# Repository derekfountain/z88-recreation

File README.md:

# z88-recreation
A recreation of the 1980's Z88 micro, using modern components

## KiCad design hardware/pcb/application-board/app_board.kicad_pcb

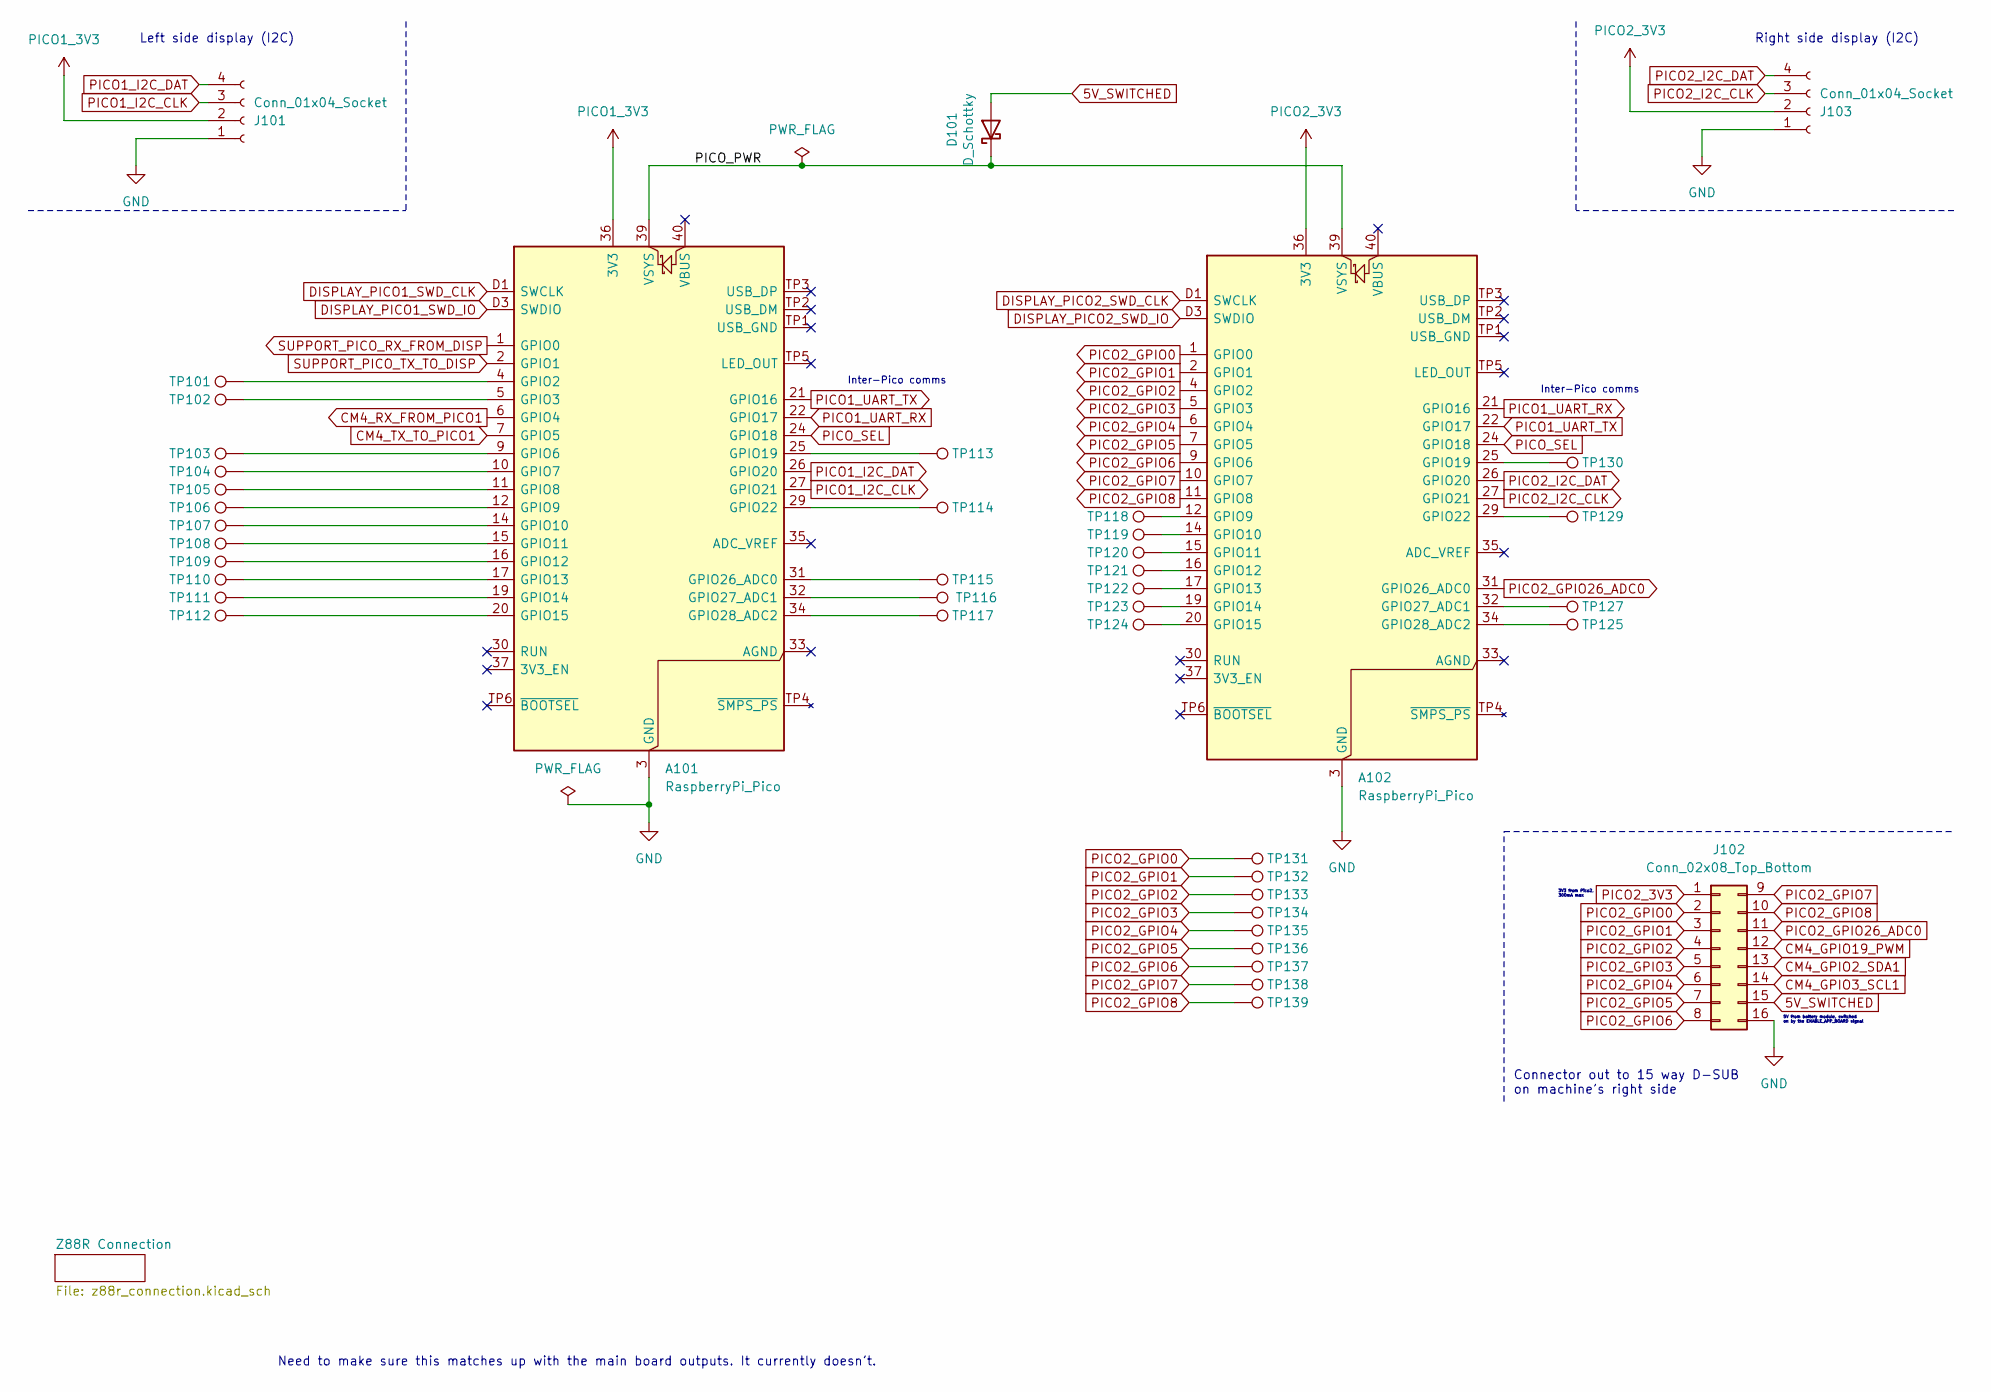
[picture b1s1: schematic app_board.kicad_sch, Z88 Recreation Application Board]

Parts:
A101, A102: RaspberryPi_Pico; RaspberryPi_Pico_Original_SMD
D101: D_Schottky; D_1206_3216Metric_Pad1.42x1.75mm_HandSolder
J101, J103: Conn_01x04_Socket; PinHeader_1x04_P2.54mm_Vertical
J102: Conn_02x08_Top_Bottom; PinHeader_2x08_P2.54mm_Vertical
TP101, TP102, TP103, TP104, TP105, TP106, TP107, TP108, TP109, TP110, TP111, TP112, TP113, TP114, TP115, TP116, TP117, TP118, TP119, TP120, TP121, TP122, TP123, TP124, TP125, TP127, TP129, TP130, TP131, TP132, TP133, TP134, TP135, TP136, TP137, TP138, TP139: TestPoint; TestPoint_THTPad_D2.0mm_Drill1.0mm

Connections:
5V_SWITCHED: D101.2 (A), J102.15; also elsewhere on the board
/PICO_PWR: A101.39 (VSYS), A102.39 (VSYS), D101.1 (K)
CM4_GPIO2_SDA1: J102.13; also elsewhere on the board
CM4_GPIO3_SCL1: J102.14; also elsewhere on the board
CM4_GPIO19_PWM: J102.12; also elsewhere on the board
CM4_RX_FROM_PICO1: A101.6 (GPIO4); also elsewhere on the board
CM4_TX_TO_PICO1: A101.7 (GPIO5); also elsewhere on the board
DISPLAY_PICO1_SWD_CLK: A101.D1 (SWCLK); also elsewhere on the board
DISPLAY_PICO1_SWD_IO: A101.D3 (SWDIO); also elsewhere on the board
DISPLAY_PICO2_SWD_CLK: A102.D1 (SWCLK); also elsewhere on the board
DISPLAY_PICO2_SWD_IO: A102.D3 (SWDIO); also elsewhere on the board
GND: A101.3 (GND), A101.8 (GND), A101.13 (GND), A101.18 (GND), A101.23 (GND), A101.28 (GND), A101.38 (GND), A101.D2 (GND), A102.3 (GND), A102.8 (GND), A102.13 (GND), A102.18 (GND), A102.23 (GND), A102.28 (GND), A102.38 (GND), A102.D2 (GND), J101.1, J102.16, J103.1; also elsewhere on the board
unnamed: A101.4 (GPIO2), TP101.1
unnamed: A101.5 (GPIO3), TP102.1
unnamed: A101.9 (GPIO6), TP103.1
unnamed: A101.10 (GPIO7), TP104.1
unnamed: A101.11 (GPIO8), TP105.1
unnamed: A101.12 (GPIO9), TP106.1
unnamed: A101.14 (GPIO10), TP107.1
unnamed: A101.15 (GPIO11), TP108.1
unnamed: A101.16 (GPIO12), TP109.1
unnamed: A101.17 (GPIO13), TP110.1
unnamed: A101.19 (GPIO14), TP111.1
unnamed: A101.20 (GPIO15), TP112.1
unnamed: A101.25 (GPIO19), TP113.1
unnamed: A101.29 (GPIO22), TP114.1
unnamed: A101.31 (GPIO26_ADC0), TP115.1
unnamed: A101.32 (GPIO27_ADC1), TP116.1
unnamed: A101.34 (GPIO28_ADC2), TP117.1
unnamed: A102.12 (GPIO9), TP118.1
unnamed: A102.14 (GPIO10), TP119.1
unnamed: A102.15 (GPIO11), TP120.1
unnamed: A102.16 (GPIO12), TP121.1
unnamed: A102.17 (GPIO13), TP122.1
unnamed: A102.19 (GPIO14), TP123.1
unnamed: A102.20 (GPIO15), TP124.1
unnamed: A102.25 (GPIO19), TP130.1
unnamed: A102.29 (GPIO22), TP129.1
unnamed: A102.32 (GPIO27_ADC1), TP127.1
unnamed: A102.34 (GPIO28_ADC2), TP125.1
PICO1_3V3: A101.36 (3V3), J101.2
PICO1_I2C_CLK: A101.27 (GPIO21), J101.3
PICO1_I2C_DAT: A101.26 (GPIO20), J101.4
PICO1_UART_RX: A101.22 (GPIO17), A102.21 (GPIO16)
PICO1_UART_TX: A101.21 (GPIO16), A102.22 (GPIO17)
PICO2_3V3: A102.36 (3V3), J102.1, J103.2
PICO2_GPIO0: A102.1 (GPIO0), J102.2, TP131.1
PICO2_GPIO1: A102.2 (GPIO1), J102.3, TP132.1
PICO2_GPIO2: A102.4 (GPIO2), J102.4, TP133.1
PICO2_GPIO3: A102.5 (GPIO3), J102.5, TP134.1
PICO2_GPIO4: A102.6 (GPIO4), J102.6, TP135.1
PICO2_GPIO5: A102.7 (GPIO5), J102.7, TP136.1
PICO2_GPIO6: A102.9 (GPIO6), J102.8, TP137.1
PICO2_GPIO7: A102.10 (GPIO7), J102.9, TP138.1
PICO2_GPIO8: A102.11 (GPIO8), J102.10, TP139.1
PICO2_GPIO26_ADC0: A102.31 (GPIO26_ADC0), J102.11
PICO2_I2C_CLK: A102.27 (GPIO21), J103.3
PICO2_I2C_DAT: A102.26 (GPIO20), J103.4
PICO_SEL: A101.24 (GPIO18), A102.24 (GPIO18); also elsewhere on the board
SUPPORT_PICO_RX_FROM_DISP: A101.1 (GPIO0); also elsewhere on the board
SUPPORT_PICO_TX_TO_DISP: A101.2 (GPIO1); also elsewhere on the board

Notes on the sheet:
3V3 from Pico2, 300mA max
Connector out to 15 way D-SUB on machine's right side
Right side display (I2C)
5V from battery module, switched on by the ENABLE_APP_BOARD signal
Inter-Pico comms
Need to make sure this matches up with the main board outputs. It currently doesn't.
Left side display (I2C)

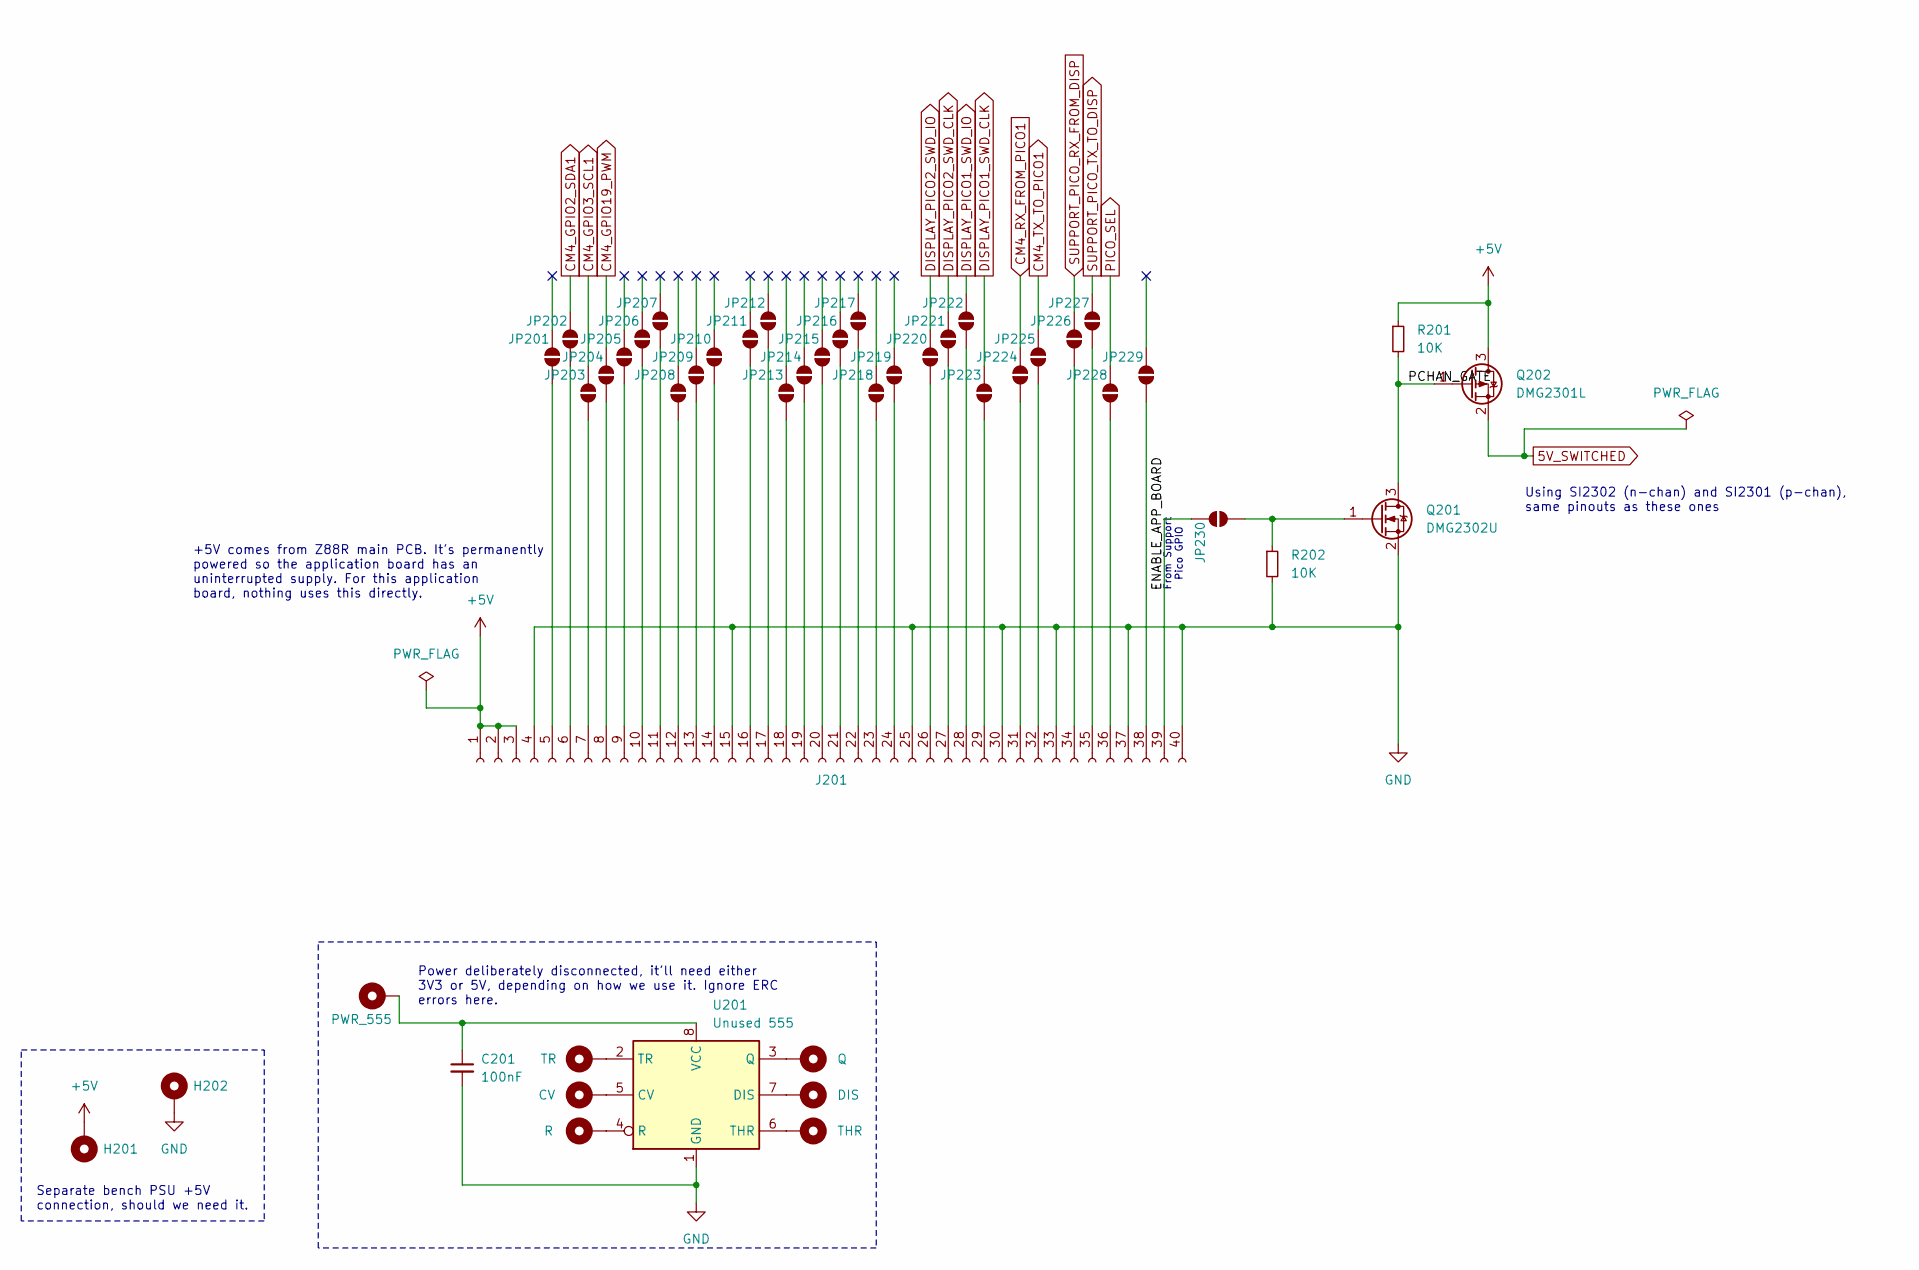
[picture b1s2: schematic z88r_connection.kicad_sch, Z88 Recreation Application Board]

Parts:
C201: 100nF; C_0805_2012Metric_Pad1.18x1.45mm_HandSolder
H201: +5V; MountingHole_2.2mm_M2_Pad
H202: GND; MountingHole_2.2mm_M2_Pad
H203: PWR_555; Pin_D0.7mm_L6.5mm_W1.8mm_FlatFork
H204: TR; Pin_D0.7mm_L6.5mm_W1.8mm_FlatFork
H205: CV; Pin_D0.7mm_L6.5mm_W1.8mm_FlatFork
H206: R; Pin_D0.7mm_L6.5mm_W1.8mm_FlatFork
H207: Q; Pin_D0.7mm_L6.5mm_W1.8mm_FlatFork
H208: DIS; Pin_D0.7mm_L6.5mm_W1.8mm_FlatFork
H209: THR; Pin_D0.7mm_L6.5mm_W1.8mm_FlatFork
J201: DISP_PCB x40 FPC; Hirose_FH12-40S-0.5SH_1x40-1MP_P0.50mm_Horizontal
JP201, JP202, JP203, JP204, JP205, JP206, JP207, JP208, JP209, JP210, JP211, JP212, JP213, JP214, JP215, JP216, JP217, JP218, JP219, JP220, JP221, JP222, JP223, JP224, JP225, JP226, JP227, JP228, JP229, JP230: SolderJumper_2_Open; SolderJumper-2_P1.3mm_Open_Pad1.0x1.5mm
Q201: DMG2302U; SOT-23
Q202: DMG2301L; SOT-23
R201, R202: 10K; R_0805_2012Metric_Pad1.20x1.40mm_HandSolder
U201: Unused 555; SOIC-8_3.9x4.9mm_P1.27mm

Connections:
5V_SWITCHED: Q202.2 (S); also elsewhere on the board
+5V: H201.1, J201.1, J201.2, J201.3, Q202.3 (D), R201.1
/Z88R Connection/ENABLE_APP_BOARD: J201.39, JP230.2 (B)
/Z88R Connection/PCHAN_GATE: Q201.3 (D), Q202.1 (G), R201.2
CM4_GPIO2_SDA1: JP202.2 (B); also elsewhere on the board
CM4_GPIO3_SCL1: JP203.2 (B); also elsewhere on the board
CM4_GPIO19_PWM: JP204.2 (B); also elsewhere on the board
CM4_RX_FROM_PICO1: JP224.2 (B); also elsewhere on the board
CM4_TX_TO_PICO1: JP225.2 (B); also elsewhere on the board
DISPLAY_PICO1_SWD_CLK: JP223.2 (B); also elsewhere on the board
DISPLAY_PICO1_SWD_IO: JP222.2 (B); also elsewhere on the board
DISPLAY_PICO2_SWD_CLK: JP221.2 (B); also elsewhere on the board
DISPLAY_PICO2_SWD_IO: JP220.2 (B); also elsewhere on the board
GND: C201.2, H202.1, J201.4, J201.15, J201.25, J201.30, J201.33, J201.37, J201.40, Q201.2 (S), R202.2, U201.1 (GND); also elsewhere on the board
unnamed: J201.5, JP201.1 (A)
unnamed: J201.6, JP202.1 (A)
unnamed: J201.7, JP203.1 (A)
unnamed: J201.8, JP204.1 (A)
unnamed: J201.9, JP205.1 (A)
unnamed: J201.10, JP206.1 (A)
unnamed: J201.11, JP207.1 (A)
unnamed: J201.12, JP208.1 (A)
unnamed: J201.13, JP209.1 (A)
unnamed: J201.14, JP210.1 (A)
unnamed: J201.16, JP211.1 (A)
unnamed: J201.17, JP212.1 (A)
unnamed: J201.18, JP213.1 (A)
unnamed: J201.19, JP214.1 (A)
unnamed: J201.20, JP215.1 (A)
unnamed: J201.21, JP216.1 (A)
unnamed: J201.22, JP217.1 (A)
unnamed: J201.23, JP218.1 (A)
unnamed: J201.24, JP219.1 (A)
unnamed: J201.26, JP220.1 (A)
unnamed: J201.27, JP221.1 (A)
unnamed: J201.28, JP222.1 (A)
unnamed: J201.29, JP223.1 (A)
unnamed: J201.31, JP224.1 (A)
unnamed: J201.32, JP225.1 (A)
unnamed: J201.34, JP226.1 (A)
unnamed: J201.35, JP227.1 (A)
unnamed: J201.36, JP228.1 (A)
unnamed: J201.38, JP229.1 (A)
unnamed: JP230.1 (A), Q201.1 (G), R202.1
unnamed: H205.1, U201.5 (CV)
unnamed: H208.1, U201.7 (DIS)
unnamed: H207.1, U201.3 (Q)
unnamed: H206.1, U201.4 (R)
unnamed: H209.1, U201.6 (THR)
unnamed: H204.1, U201.2 (TR)
unnamed: C201.1, H203.1, U201.8 (VCC)
PICO_SEL: JP228.2 (B); also elsewhere on the board
SUPPORT_PICO_RX_FROM_DISP: JP226.2 (B); also elsewhere on the board
SUPPORT_PICO_TX_TO_DISP: JP227.2 (B); also elsewhere on the board

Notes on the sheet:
Separate bench PSU +5V connection, should we need it.
Using SI2302 (n-chan) and SI2301 (p-chan), same pinouts as these ones
Power deliberately disconnected, it'll need either 3V3 or 5V, depending on how we use it. Ignore ERC errors here.
+5V comes from Z88R main PCB. It's permanently powered so the application board has an uninterrupted supply. For this application board, nothing uses this directly.
From Support Pico GPIO

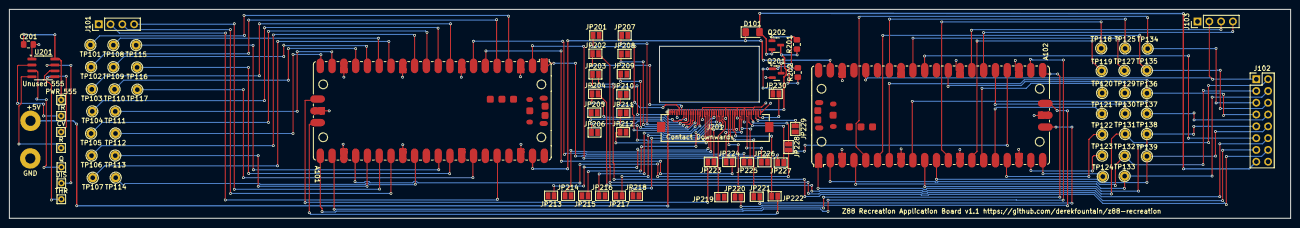
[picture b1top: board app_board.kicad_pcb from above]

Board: 2 copper layers, 276.0 x 45.0 mm, 89 parts (0 on the bottom side), 101 nets.

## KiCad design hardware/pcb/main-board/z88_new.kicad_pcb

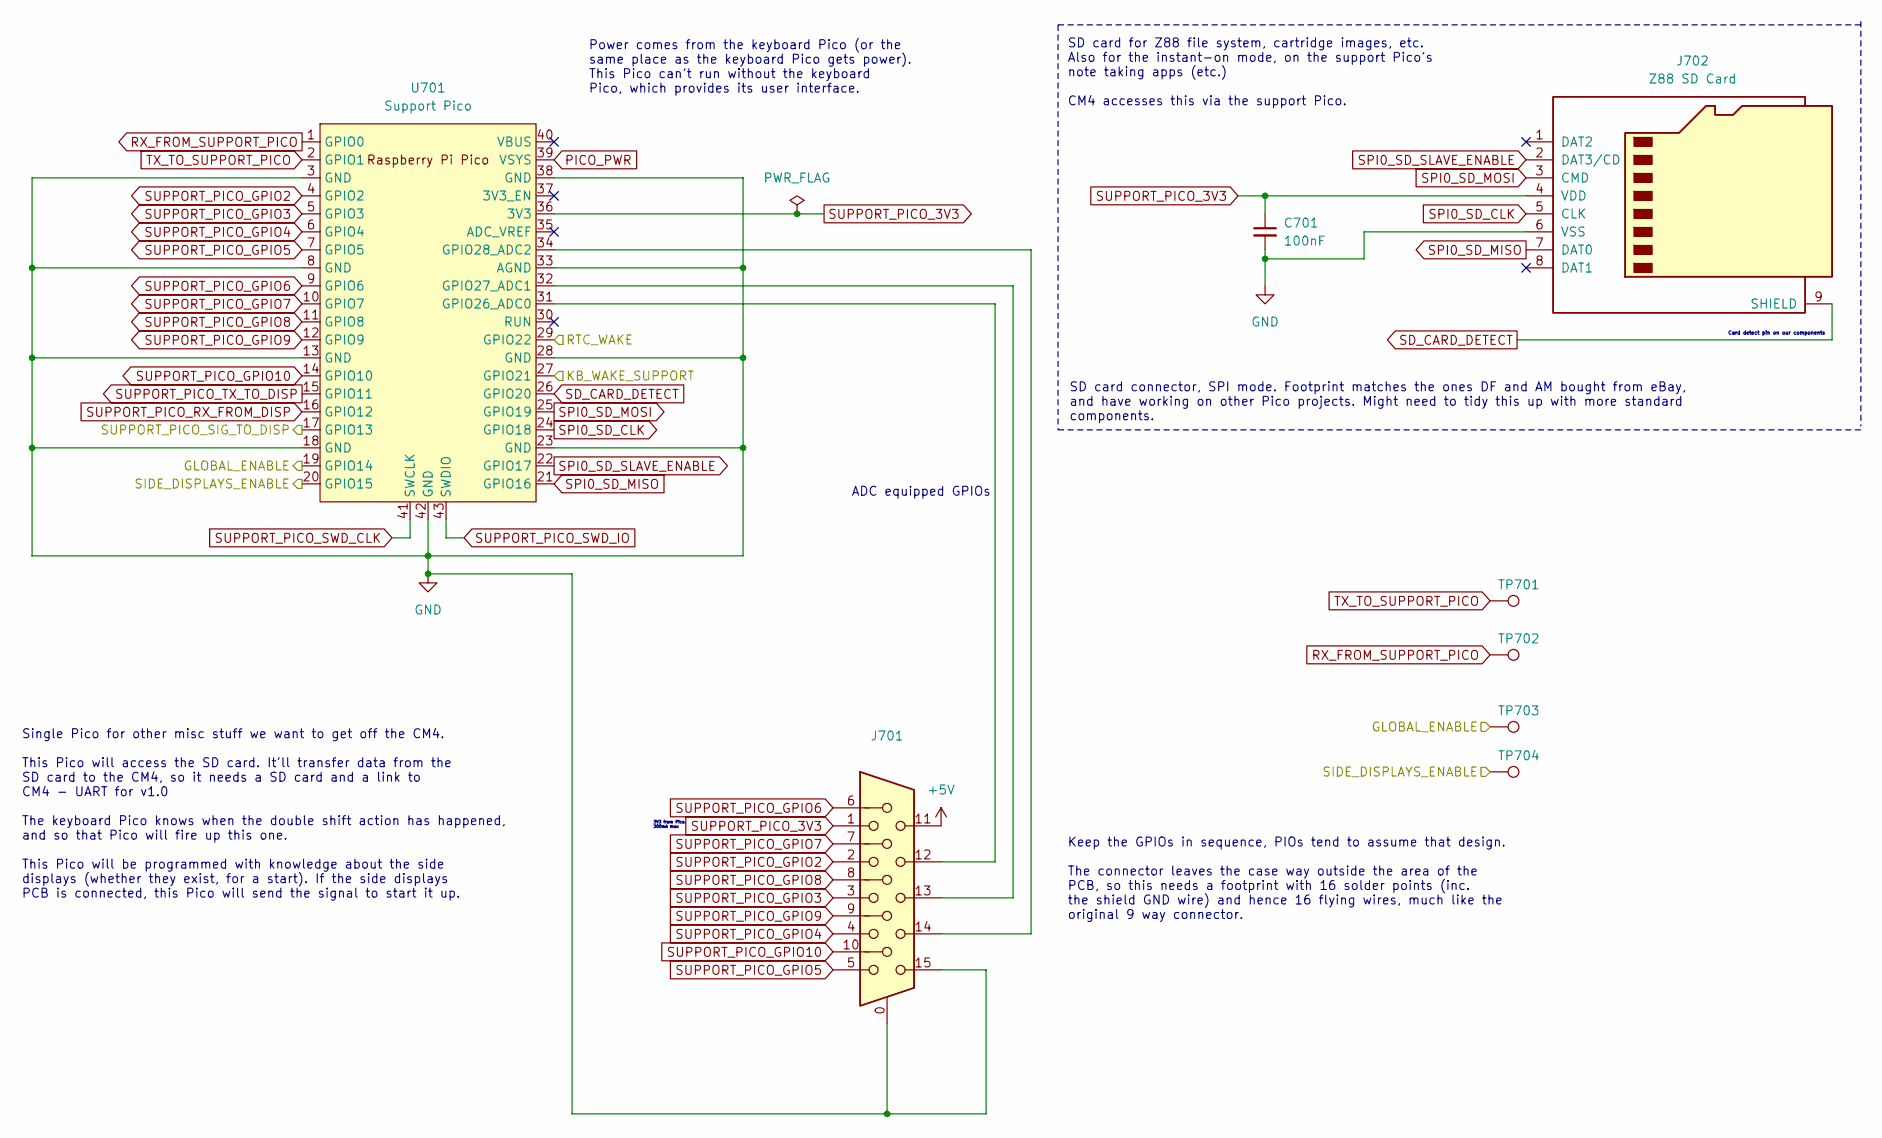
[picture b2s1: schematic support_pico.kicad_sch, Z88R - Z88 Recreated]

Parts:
C701: 100nF; C_0805_2012Metric_Pad1.18x1.45mm_HandSolder
J701: DE15_Receptacle_HighDensity_MountingHoles; DSUB-15-HD_Female_Vertical_P2.29x1.98mm_MountingHoles
J702: Z88 SD Card; Conn_uSDcard
TP701: TX to SP; TestPoint_THTPad_D2.0mm_Drill1.0mm
TP702: RX fr SP; TestPoint_THTPad_D2.0mm_Drill1.0mm
TP703: GL EN; TestPoint_THTPad_D2.0mm_Drill1.0mm
TP704: SIDE DISP EN; TestPoint_THTPad_D2.0mm_Drill1.0mm
U701: Support Pico; RPi_Pico_SMD_TH

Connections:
+5V: J701.11; also elsewhere on the board
/CM4_GPIO/GLOBAL_ENABLE: TP703.1, U701.19 (GPIO14); also elsewhere on the board
/Keyboard/KB_WAKE_SUPPORT: U701.27 (GPIO21); also elsewhere on the board
/Power/RTC_WAKE: U701.29 (GPIO22); also elsewhere on the board
/Side Displays/SIDE_DISPLAYS_ENABLE: TP704.1, U701.20 (GPIO15); also elsewhere on the board
/Side Displays/SUPPORT_PICO_SIG_TO_DISP: U701.17 (GPIO13); also elsewhere on the board
GND: C701.2, J701.0, J701.15, J702.6 (VSS), U701.3 (GND), U701.8 (GND), U701.13 (GND), U701.18 (GND), U701.23 (GND), U701.28 (GND), U701.33 (AGND), U701.38 (GND), U701.42 (GND); also elsewhere on the board
unnamed: J701.12, U701.31 (GPIO26_ADC0)
unnamed: J701.13, U701.32 (GPIO27_ADC1)
unnamed: J701.14, U701.34 (GPIO28_ADC2)
PICO_PWR: U701.39 (VSYS); also elsewhere on the board
RX_FROM_SUPPORT_PICO: TP702.1, U701.1 (GPIO0); also elsewhere on the board
SD_CARD_DETECT: J702.9 (SHIELD), U701.26 (GPIO20)
SPI0_SD_CLK: J702.5 (CLK), U701.24 (GPIO18)
SPI0_SD_MISO: J702.7 (DAT0), U701.21 (GPIO16)
SPI0_SD_MOSI: J702.3 (CMD), U701.25 (GPIO19)
SPI0_SD_SLAVE_ENABLE: J702.2 (DAT3/CD), U701.22 (GPIO17)
SUPPORT_PICO_3V3: C701.1, J701.1, J702.4 (VDD), U701.36 (3V3); also elsewhere on the board
SUPPORT_PICO_GPIO2: J701.2, U701.4 (GPIO2); also elsewhere on the board
SUPPORT_PICO_GPIO3: J701.3, U701.5 (GPIO3); also elsewhere on the board
SUPPORT_PICO_GPIO4: J701.4, U701.6 (GPIO4); also elsewhere on the board
SUPPORT_PICO_GPIO5: J701.5, U701.7 (GPIO5); also elsewhere on the board
SUPPORT_PICO_GPIO6: J701.6, U701.9 (GPIO6); also elsewhere on the board
SUPPORT_PICO_GPIO7: J701.7, U701.10 (GPIO7); also elsewhere on the board
SUPPORT_PICO_GPIO8: J701.8, U701.11 (GPIO8); also elsewhere on the board
SUPPORT_PICO_GPIO9: J701.9, U701.12 (GPIO9); also elsewhere on the board
SUPPORT_PICO_GPIO10: J701.10, U701.14 (GPIO10); also elsewhere on the board
SUPPORT_PICO_RX_FROM_DISP: U701.16 (GPIO12); also elsewhere on the board
SUPPORT_PICO_SWD_CLK: U701.41 (SWCLK); also elsewhere on the board
SUPPORT_PICO_SWD_IO: U701.43 (SWDIO); also elsewhere on the board
SUPPORT_PICO_TX_TO_DISP: U701.15 (GPIO11); also elsewhere on the board
TX_TO_SUPPORT_PICO: TP701.1, U701.2 (GPIO1); also elsewhere on the board

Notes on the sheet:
SD card for Z88 file system, cartridge images, etc. Also for the instant-on mode, on the support Pico's note taking apps (etc.) CM4 accesses this via the support Pico.
ADC equipped GPIOs
Power comes from the keyboard Pico (or the same place as the keyboard Pico gets power). This Pico can't run without the keyboard Pico, which provides its user interface.
Keep the GPIOs in sequence, PIOs tend to assume that design. The connector leaves the case way outside the area of the PCB, so this needs a footprint with 16 solder points (inc. the shield GND wire) and hence 16 flying wires, much like the original 9 way connector.
3V3 from Pico, 300mA max
Card detect pin on our components
Single Pico for other misc stuff we want to get off the CM4. This Pico will access the SD card. It'll transfer data from the SD card to the CM4, so it needs a SD card and a link to CM4 - UART for v1.0 The keyboard Pico knows when the double shift action has happened, and so that Pico will fire up t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
SD card connector, SPI mode. Footprint matches the ones DF and AM bought from eBay, and have working on other Pico projects. Might need to tidy this up with more standard components.

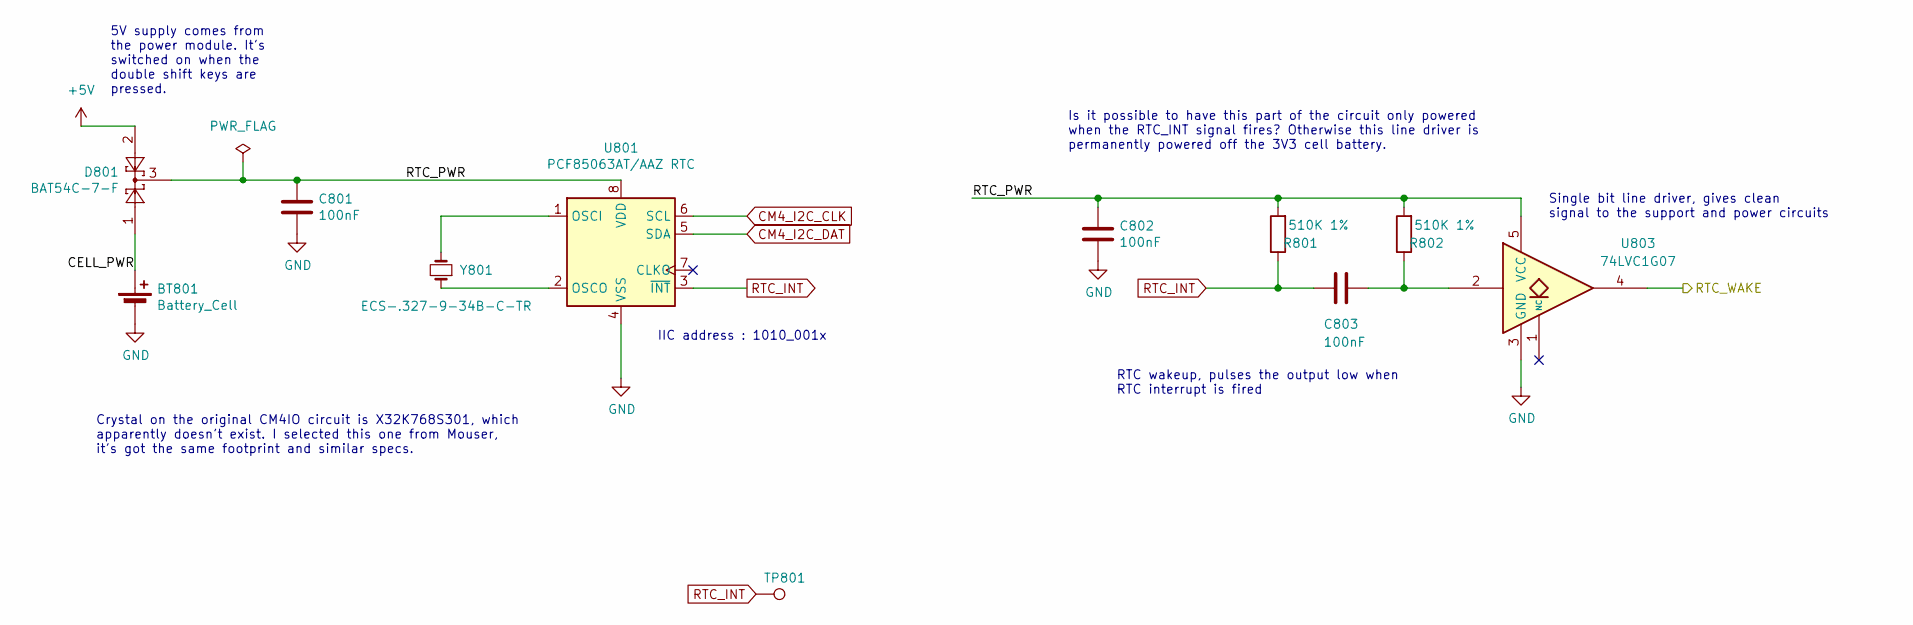
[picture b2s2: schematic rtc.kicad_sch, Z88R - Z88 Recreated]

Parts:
BT801: Battery_Cell; BatteryHolder_Keystone_3034_1x20mm; Part Description Battery Retainer Coin, 20.0mm 1 Cell SM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
C801, C802, C803: 100nF; C_0805_2012Metric_Pad1.18x1.45mm_HandSolder; Part Description 0.1uF 10% 16V Ceramic Capacitor X7R 040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
D801: BAT54C-7-F; SOT-23; Part Description Diode Array 1 Pair Common Cathode Schot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
R801, R802: 510K 1%; R_0805_2012Metric_Pad1.20x1.40mm_HandSolder; Part Description Resistor 510K M1005 1% 63mW
TP801: RTC INT; TestPoint_THTPad_D2.0mm_Drill1.0mm
U801: PCF85063AT/AAZ RTC; SOIC-8_3.9x4.9mm_P1.27mm; Part Description Real Time Clock (RTC) IC Clock/Calendar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
U803: 74LVC1G07; SOT-353_SC-70-5
Y801: ECS-.327-9-34B-C-TR; Crystal_SMD_3215-2Pin_3.2x1.5mm; Part Description Crystal 32.768KHz 7pF 20pmm

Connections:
+5V: D801.2; also elsewhere on the board
/Power/RTC_WAKE: U803.4; also elsewhere on the board
/RTC/CELL_PWR: BT801.1 (+), D801.1
/RTC/RTC_PWR: C801.1, C802.1, D801.3, R801.2, R802.2, U801.8 (VDD), U803.5 (VCC)
CM4_I2C_CLK: U801.6 (SCL); also elsewhere on the board
CM4_I2C_DAT: U801.5 (SDA); also elsewhere on the board
GND: BT801.2 (-), C801.2, C802.2, U801.4 (VSS), U803.3 (GND); also elsewhere on the board
unnamed: C803.1, R802.1, U803.2
unnamed: U801.1 (OSCI), Y801.2
unnamed: U801.2 (OSCO), Y801.1
RTC_INT: C803.2, R801.1, TP801.1, U801.3 (~INT)

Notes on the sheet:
RTC wakeup, pulses the output low when RTC interrupt is fired
5V supply comes from the power module. It's switched on when the double shift keys are pressed.
Single bit line driver, gives clean signal to the support and power circuits
Crystal on the original CM4IO circuit is X32K768S301, which apparently doesn't exist. I selected this one from Mouser, it's got the same footprint and similar specs.
Is it possible to have this part of the circuit only powered when the RTC_INT signal fires? Otherwise this line driver is permanently powered off the 3V3 cell battery.
IIC address : 1010_001x

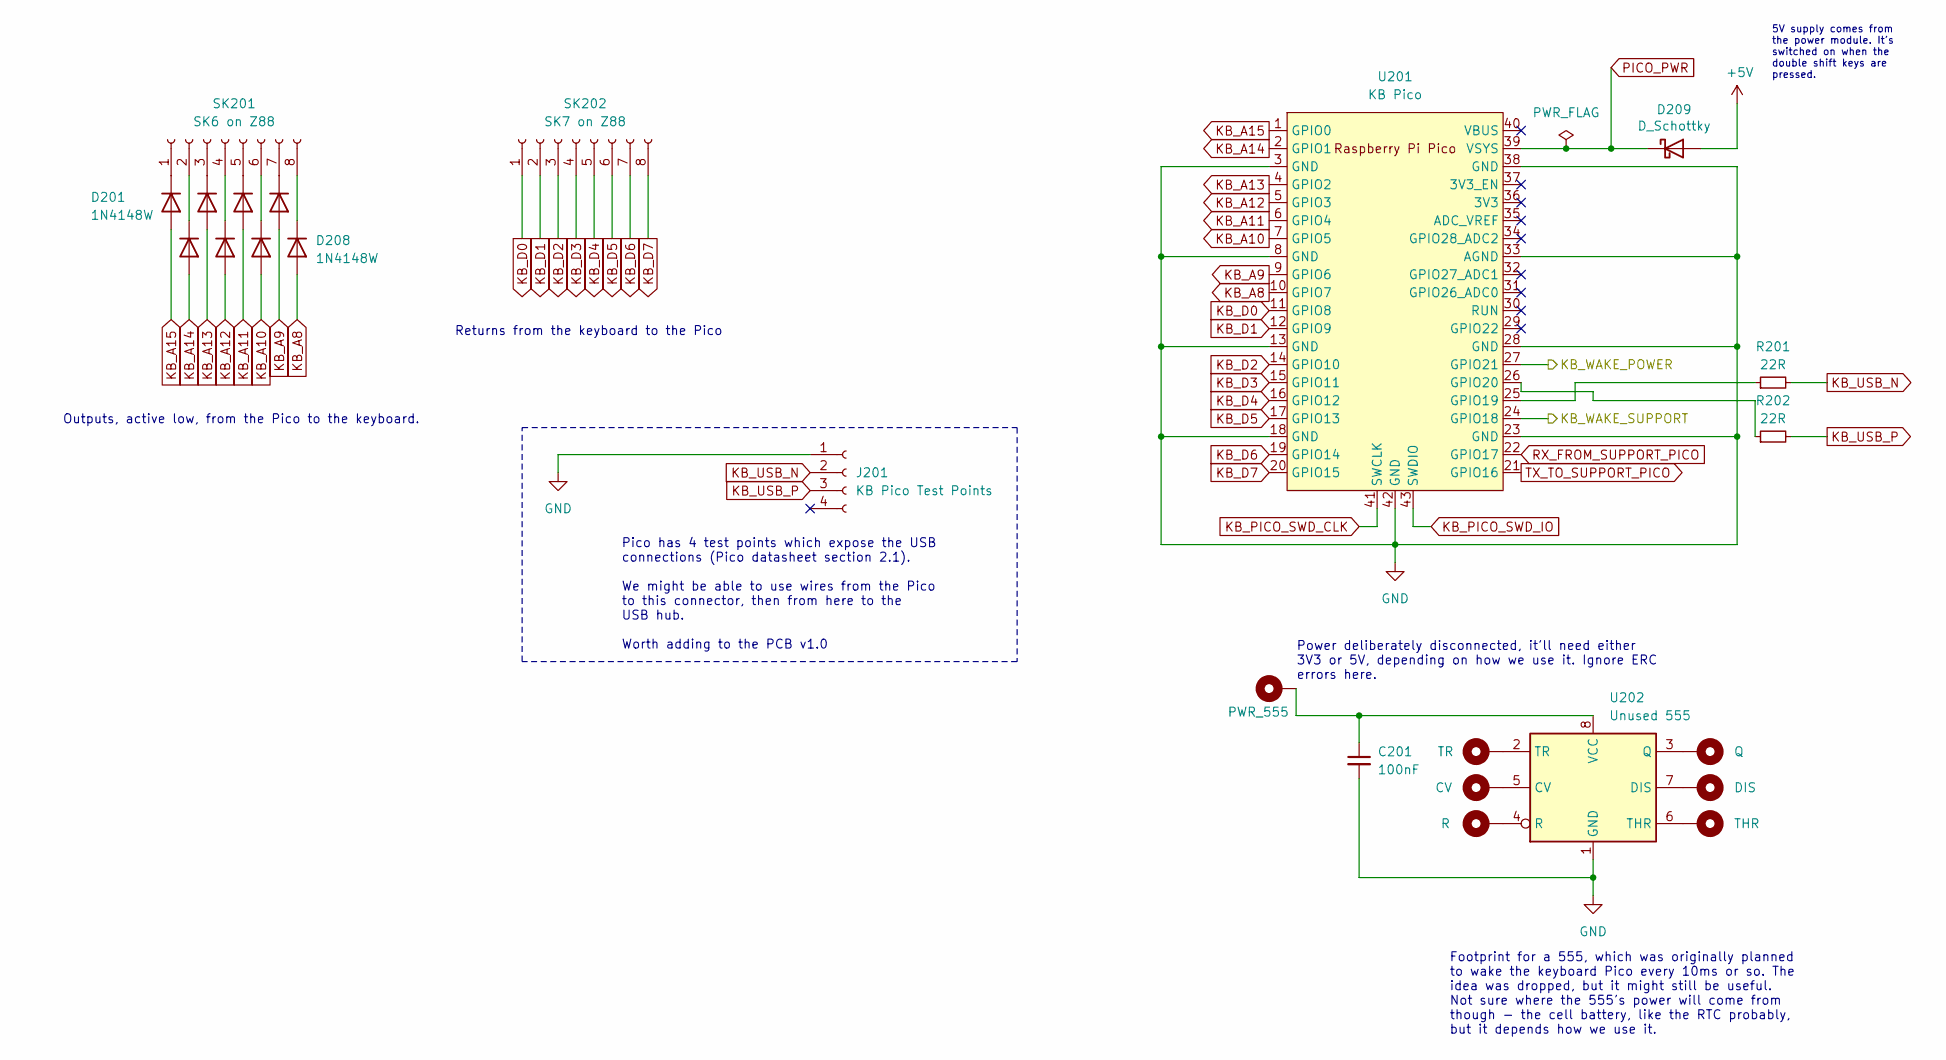
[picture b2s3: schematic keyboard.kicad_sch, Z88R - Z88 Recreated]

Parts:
C201: 100nF; C_0805_2012Metric_Pad1.18x1.45mm_HandSolder
D201, D202, D203, D204, D205, D206, D207, D208: 1N4148W; D_SOD-123
D209: D_Schottky; D_1206_3216Metric_Pad1.42x1.75mm_HandSolder
H201: TR; Pin_D0.7mm_L6.5mm_W1.8mm_FlatFork
H202: CV; Pin_D0.7mm_L6.5mm_W1.8mm_FlatFork
H203: R; Pin_D0.7mm_L6.5mm_W1.8mm_FlatFork
H204: Q; Pin_D0.7mm_L6.5mm_W1.8mm_FlatFork
H205: DIS; Pin_D0.7mm_L6.5mm_W1.8mm_FlatFork
H206: THR; Pin_D0.7mm_L6.5mm_W1.8mm_FlatFork
H207: PWR_555; Pin_D0.7mm_L6.5mm_W1.8mm_FlatFork
J201: KB Pico Test Points; PinHeader_1x04_P1.00mm_Vertical
R201, R202: 22R; R_0805_2012Metric_Pad1.20x1.40mm_HandSolder
SK201: SK6 on Z88; PinSocket_1x08_P2.54mm_Vertical
SK202: SK7 on Z88; PinSocket_1x08_P2.54mm_Vertical
U201: KB Pico; RPi_Pico_SMD_TH
U202: Unused 555; SOIC-8_3.9x4.9mm_P1.27mm

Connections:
+5V: D209.2 (A); also elsewhere on the board
/Keyboard/KB_WAKE_POWER: U201.27 (GPIO21); also elsewhere on the board
/Keyboard/KB_WAKE_SUPPORT: U201.24 (GPIO18); also elsewhere on the board
GND: C201.2, J201.1, U201.3 (GND), U201.8 (GND), U201.13 (GND), U201.18 (GND), U201.23 (GND), U201.28 (GND), U201.33 (AGND), U201.38 (GND), U201.42 (GND), U202.1 (GND); also elsewhere on the board
KB_A8: D208.2 (A), U201.10 (GPIO7)
KB_A9: D207.2 (A), U201.9 (GPIO6)
KB_A10: D206.2 (A), U201.7 (GPIO5)
KB_A11: D205.2 (A), U201.6 (GPIO4)
KB_A12: D204.2 (A), U201.5 (GPIO3)
KB_A13: D203.2 (A), U201.4 (GPIO2)
KB_A14: D202.2 (A), U201.2 (GPIO1)
KB_A15: D201.2 (A), U201.1 (GPIO0)
KB_D0: SK202.1, U201.11 (GPIO8)
KB_D1: SK202.2, U201.12 (GPIO9)
KB_D2: SK202.3, U201.14 (GPIO10)
KB_D3: SK202.4, U201.15 (GPIO11)
KB_D4: SK202.5, U201.16 (GPIO12)
KB_D5: SK202.6, U201.17 (GPIO13)
KB_D6: SK202.7, U201.19 (GPIO14)
KB_D7: SK202.8, U201.20 (GPIO15)
KB_PICO_SWD_CLK: U201.41 (SWCLK); also elsewhere on the board
KB_PICO_SWD_IO: U201.43 (SWDIO); also elsewhere on the board
KB_USB_N: J201.2, R201.2; also elsewhere on the board
KB_USB_P: J201.3, R202.2; also elsewhere on the board
unnamed: D201.1 (K), SK201.1
unnamed: D202.1 (K), SK201.2
unnamed: D203.1 (K), SK201.3
unnamed: D204.1 (K), SK201.4
unnamed: D205.1 (K), SK201.5
unnamed: D206.1 (K), SK201.6
unnamed: D207.1 (K), SK201.7
unnamed: D208.1 (K), SK201.8
unnamed: R201.1, U201.25 (GPIO19)
unnamed: R202.1, U201.26 (GPIO20)
unnamed: H202.1, U202.5 (CV)
unnamed: H205.1, U202.7 (DIS)
unnamed: H204.1, U202.3 (Q)
unnamed: H203.1, U202.4 (R)
unnamed: H206.1, U202.6 (THR)
unnamed: H201.1, U202.2 (TR)
unnamed: C201.1, H207.1, U202.8 (VCC)
PICO_PWR: D209.1 (K), U201.39 (VSYS); also elsewhere on the board
RX_FROM_SUPPORT_PICO: U201.22 (GPIO17); also elsewhere on the board
TX_TO_SUPPORT_PICO: U201.21 (GPIO16); also elsewhere on the board

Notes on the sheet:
Returns from the keyboard to the Pico
Pico has 4 test points which expose the USB connections (Pico datasheet section 2.1). We might be able to use wires from the Pico to this connector, then from here to the USB hub. Worth adding to the PCB v1.0
Power deliberately disconnected, it'll need either 3V3 or 5V, depending on how we use it. Ignore ERC errors here.
5V supply comes from the power module. It's switched on when the double shift keys are pressed.
Footprint for a 555, which was originally planned to wake the keyboard Pico every 10ms or so. The idea was dropped, but it might still be useful. Not sure where the 555's power will come from though - the cell battery, like the RTC probably, but it depends how we use it.
Outputs, active low, from the Pico to the keyboard.
